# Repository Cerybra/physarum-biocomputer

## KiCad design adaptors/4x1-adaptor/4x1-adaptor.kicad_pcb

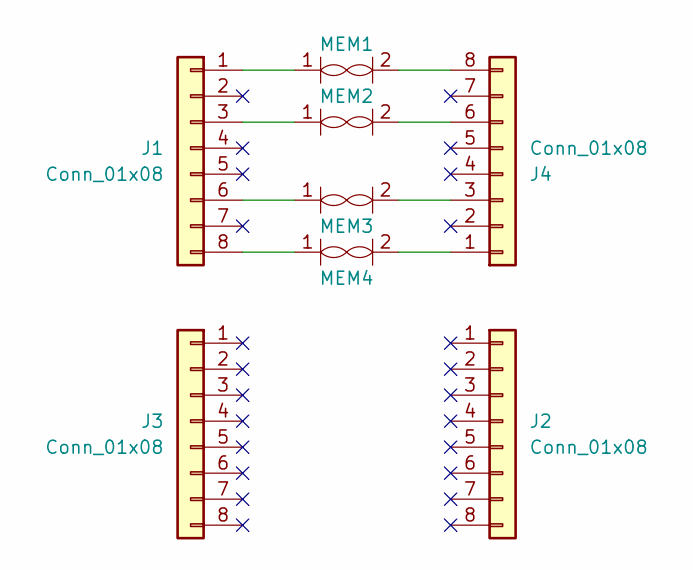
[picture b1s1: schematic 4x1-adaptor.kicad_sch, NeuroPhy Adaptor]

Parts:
J1, J2, J3, J4: Conn_01x08; PinHeader_1x08_P2.54mm_Vertical
MEM1, MEM2, MEM3, MEM4: NeuroPhy_Memristor_5x5mm

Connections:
unnamed: J1.1, MEM1.1
unnamed: J1.3, MEM2.1
unnamed: J1.6, MEM3.1
unnamed: J1.8, MEM4.1
unnamed: J4.1, MEM4.2
unnamed: J4.3, MEM3.2
unnamed: J4.6, MEM2.2
unnamed: J4.8, MEM1.2

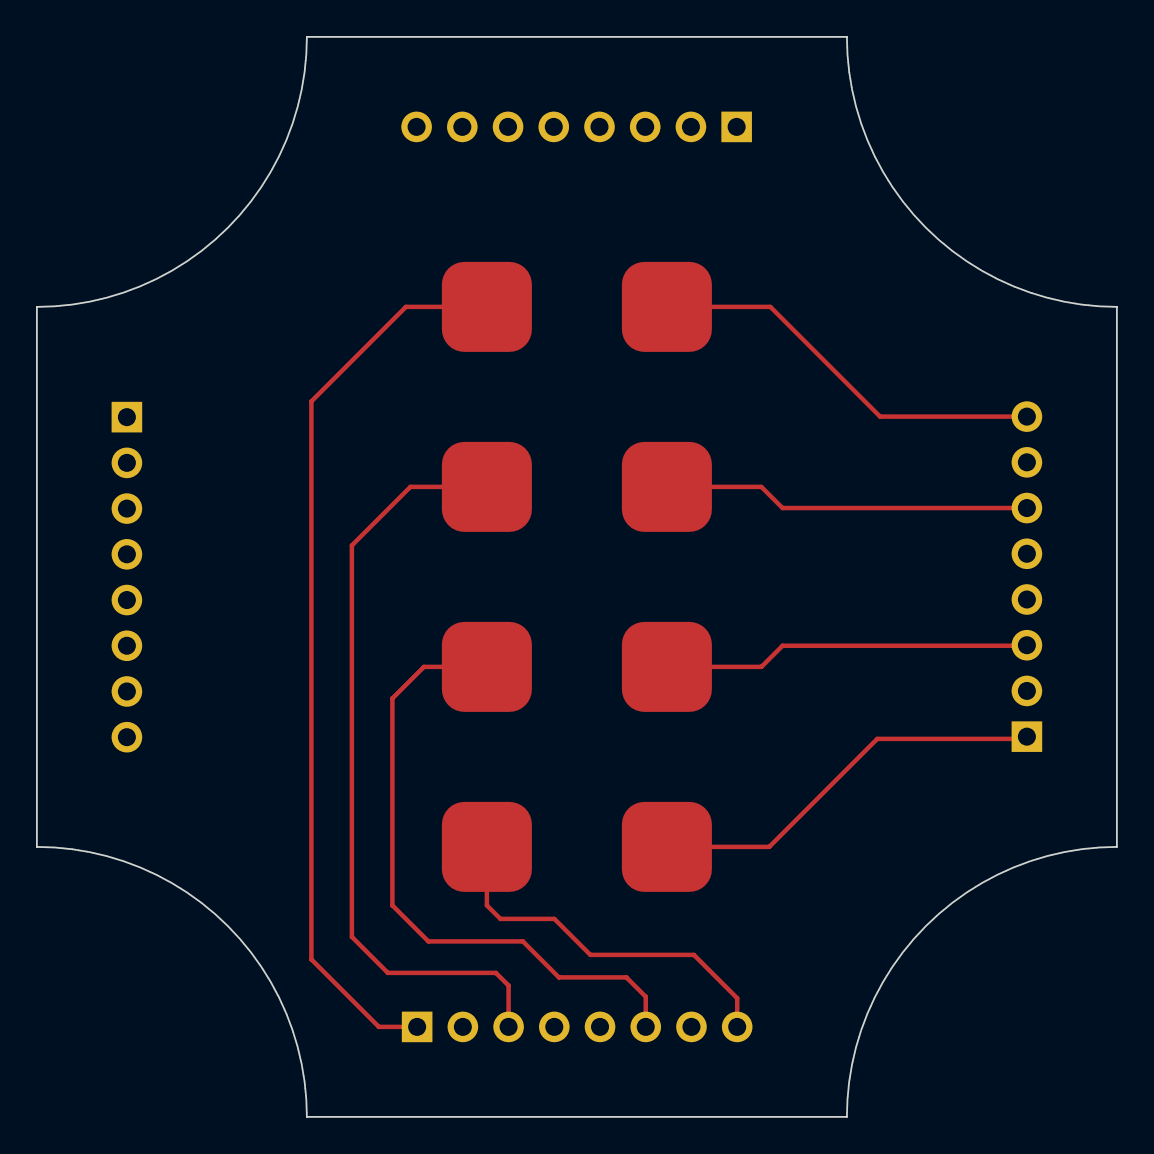
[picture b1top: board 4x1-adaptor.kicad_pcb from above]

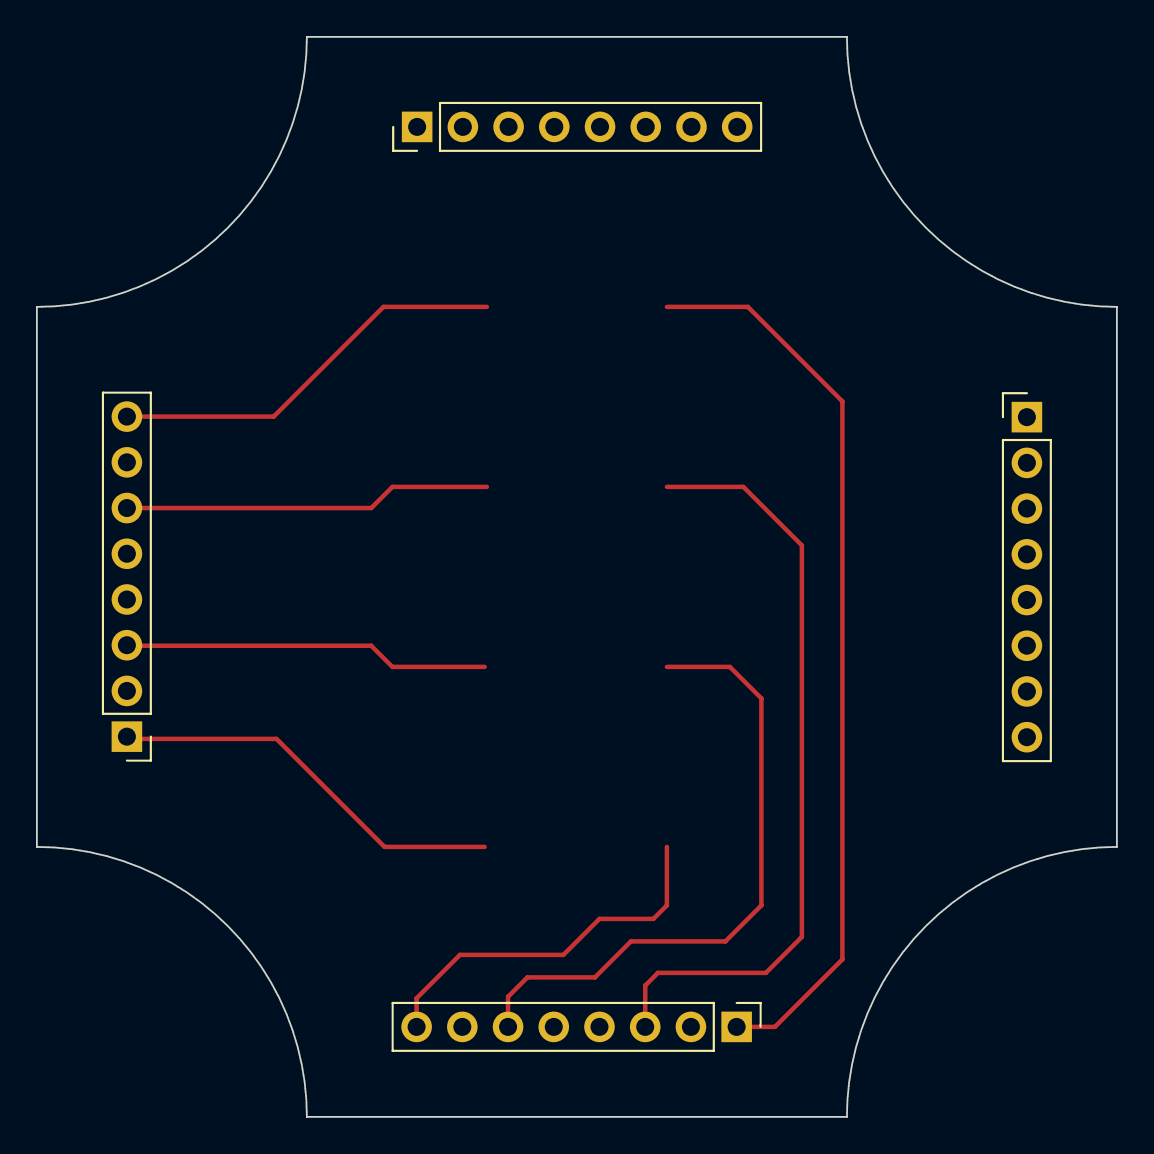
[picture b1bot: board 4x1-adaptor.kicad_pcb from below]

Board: 2 copper layers, 60.0 x 60.0 mm, 8 parts (4 on the bottom side), 8 nets.

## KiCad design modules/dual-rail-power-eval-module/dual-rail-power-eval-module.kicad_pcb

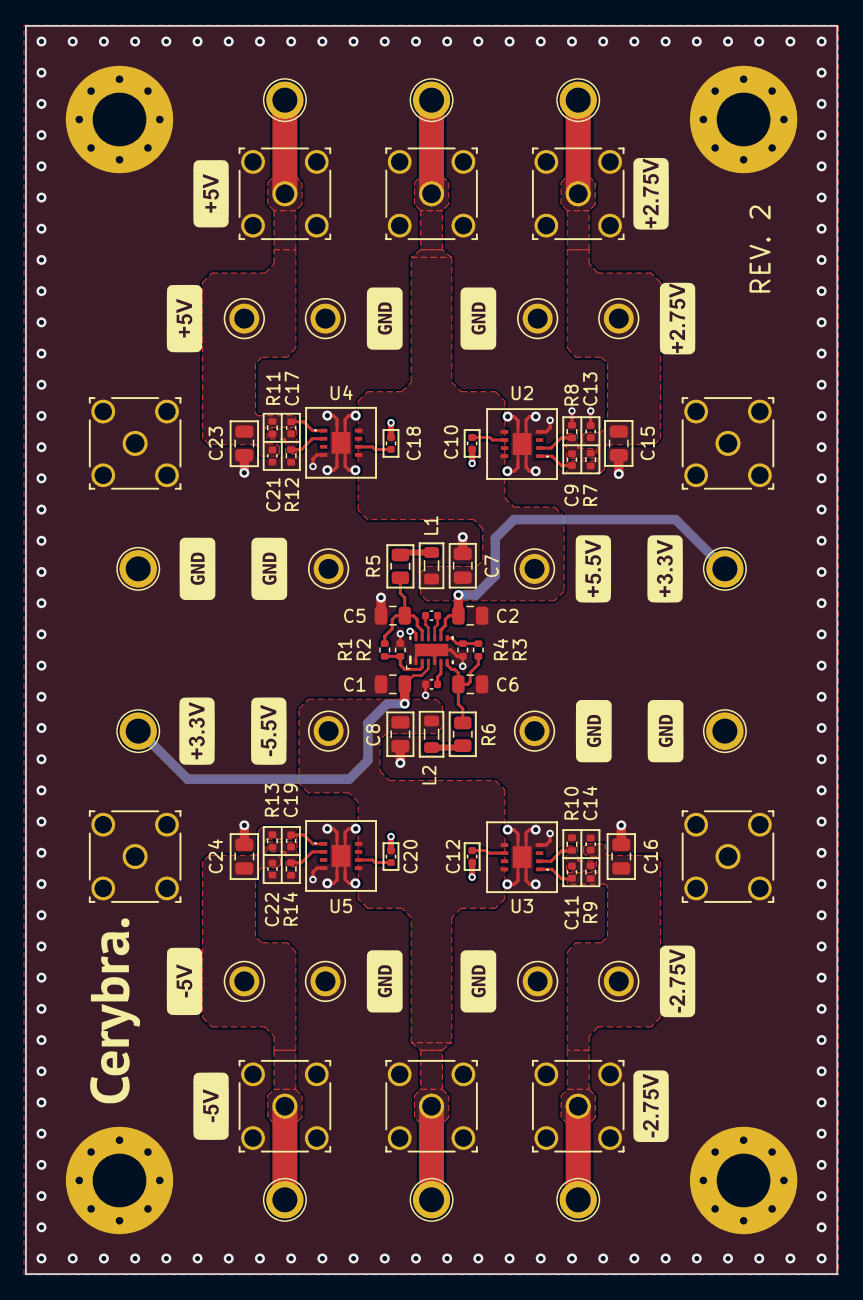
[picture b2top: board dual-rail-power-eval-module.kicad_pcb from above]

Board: 4 copper layers, 65.0 x 100.0 mm, 81 parts (0 on the bottom side), 25 nets.

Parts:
C1, C2, C15, C16, C23, C24: 10uF; C_0805_2012Metric
C3: 1uF; C_0402_1005Metric
C4: 4.7uF; C_0402_1005Metric
C5, C6: 22uF; C_0805_2012Metric
C7, C8: 100uF; C_0805_2012Metric
C9, C10, C11, C12, C17, C18, C19, C20: 10nF; C_0402_1005Metric
C13, C14, C21, C22: 100nF; C_0402_1005Metric
H1, H2, H3, H4: MountingHole_Pad; MountingHole_4.3mm_M4_Pad_Via
J1, J2, J3, J4, J5, J6, J7, J8, J9, J10: Conn_Coaxial; CONN_RF2-04A-T-00-50-G_ADM
L1, L2: 100uH; L_0805_2012Metric
R1, R3: 221k; R_0402_1005Metric
R2: 68.9k; R_0402_1005Metric
R4: 69.8k; R_0402_1005Metric
R5, R6: 1.3; R_0805_2012Metric
R7, R9: 47k; R_0402_1005Metric
R8, R10: 35k7; R_0402_1005Metric
R11, R13: 97k6; R_0402_1005Metric
R12, R14: 30k1; R_0402_1005Metric
TP1, TP2, TP3, TP4, TP5, TP6: TestPoint; KEYSTONE_5000
TP7, TP8, TP9, TP10, TP11, TP12: TestPoint; KEYSTONE_5006
TP13, TP14, TP15, TP16, TP17, TP18, TP19, TP20, TP21, TP22: Turret; TestPoint_Plated_Hole_D2.0mm
U1: LM27762; DSS0012B
U2, U4: TPS7A4901DRBR; VSON-8
U3, U5: TPS7A3001DRBR; VSON-8

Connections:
/+2.75V: C9.1, C13.1, C15.1, J3.1 (In), R7.2, TP3.1, TP16.1, U2.1 (OUT)
/+2.75V_REG_FB: C9.2, R7.1, R8.2, U2.2 (FB)
/+2.75V_REG_NR/SS: C10.1, U2.6 (NR/SS)
/+3.3V: C1.1, C2.1, TP13.1, TP17.1, U1.3 (VIN), U1.8 (EN-), U1.12 (EN+)
/+5.5V: C7.1, J1.1 (In), L1.2, TP1.1, TP14.1, U2.5 (EN), U2.8 (IN), U4.5 (EN), U4.8 (IN)
/+5V: C17.1, C21.1, C23.1, J5.1 (In), R11.2, TP5.1, TP15.1, U4.1 (OUT)
/+5V_REG_FB: C17.2, R11.1, R12.2, U4.2 (FB)
/+5V_REG_NR/SS: C18.1, U4.6 (NR/SS)
/-2.75V: C11.1, C14.1, C16.1, J4.1 (In), R9.2, TP4.1, TP20.1, U3.1 (OUT)
/-2.75V_REG_FB: C11.2, R9.1, R10.2, U3.2 (FB)
/-2.75V_REG_NR/SS: C12.1, U3.6 (NR/SS)
/-5.5V: C8.1, J2.1 (In), L2.2, TP2.1, TP18.1, U3.5 (EN), U3.8 (IN), U5.5 (EN), U5.8 (IN)
/-5V: C19.1, C22.1, C24.1, J6.1 (In), R13.2, TP6.1, TP19.1, U5.1 (OUT)
/-5V_REG_FB: C19.2, R13.1, R14.2, U5.2 (FB)
/-5V_REG_NR/SS: C20.1, U5.6 (NR/SS)
/C1+: C3.2, U1.10 (C1+)
/C1-: C3.1, U1.9 (C1-)
/CP_CAP: C4.1, U1.5 (CP)
/CP_NEG_FB: R3.1, R4.2, U1.7 (FB-)
/CP_NEG_OUT: C6.1, R3.2, R6.2, U1.6 (OUT-)
/CP_POS_FB: R1.1, R2.2, U1.2 (FB+)
/CP_POS_OUT: C5.1, R1.2, R5.2, U1.11 (OUT+)
Earth: C1.2, C2.2, C4.2, C5.2, C6.2, C7.2, C8.2, C10.2, C12.2, C13.2, C14.2, C15.2, C16.2, C18.2, C20.2, C21.2, C22.2, C23.2, C24.2, H1.1, H2.1, H3.1, H4.1, J1.2 (Ext), J2.2 (Ext), J3.2 (Ext), J4.2 (Ext), J5.2 (Ext), J6.2 (Ext), J7.1 (In), J7.2 (Ext), J8.1 (In), J8.2 (Ext), J9.1 (In), J9.2 (Ext), J10.1 (In), J10.2 (Ext), R2.1, R4.1, R8.1, R10.1, R12.1, R14.1, TP7.1, TP8.1, TP9.1, TP10.1, TP11.1, TP12.1, TP21.1, TP22.1, U1.1 (PGOOD), U1.4 (GND), U1.13 (GND), U2.4 (GND), U2.9 (EP), U2.10 (EP), U2.11 (EP), U2.12 (EP), U2.13 (EP), U3.4 (GND), U3.9 (EP), U3.10 (EP), U3.11 (EP), U3.12 (EP), U3.13 (EP), U4.4 (GND), U4.9 (EP), U4.10 (EP), U4.11 (EP), U4.12 (EP), U4.13 (EP), U5.4 (GND), U5.9 (EP), U5.10 (EP), U5.11 (EP), U5.12 (EP), U5.13 (EP)
unnamed: L1.1, R5.1
unnamed: L2.1, R6.1

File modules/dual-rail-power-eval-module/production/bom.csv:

Comment,Designator,Footprint,LCSC Part #
10uF Unpolarized capacitor,"C1,C2,C15,C16,C23,C24",C_0805_2012Metric,
1uF Unpolarized capacitor,C3,C_0402_1005Metric,
4.7uF Unpolarized capacitor,C4,C_0402_1005Metric,
22uF Unpolarized capacitor,"C5,C6",C_0805_2012Metric,
100uF Unpolarized capacitor,"C7,C8",C_0805_2012Metric,
10nF Unpolarized capacitor,"C9,C10,C11,C12,C17,C18,C19,C20",C_0402_1005Metric,
100nF Unpolarized capacitor,"C13,C14,C21,C22",C_0402_1005Metric,
"Conn_Coaxial coaxial connector (BNC, SMA, SMB, SMC, Cinch/RCA, LEMO, ...)","J1,J2,J3,J4,J5,J6,J7,J8,J9,J10",CONN_RF2-04A-T-00-50-G_ADM,C496549
100uH Inductor,"L1,L2",L_0805_2012Metric,
221k Resistor,"R1,R3",R_0402_1005Metric,
68k1 Resistor,R2,R_0402_1005Metric,
69k8 Resistor,R4,R_0402_1005Metric,
1.3 Resistor,"R5,R6",R_0805_2012Metric,
47k Resistor,"R7,R9",R_0402_1005Metric,
35k7 Resistor,"R8,R10",R_0402_1005Metric,
97k6 Resistor,"R11,R13",R_0402_1005Metric,
30k1 Resistor,"R12,R14",R_0402_1005Metric,
TestPoint test point,"TP1,TP2,TP3,TP4,TP5,TP6",KEYSTONE_5000,C5199900
TestPoint test point,"TP7,TP8,TP9,TP10,TP11,TP12",KEYSTONE_5006,C2906764
LM27762 ,U1,DSS0012B,
"TPS7A4901DRBR 36-V, 150-mA, Ultralow-Noise, Positive Linear Regulator","U2,U4",VSON-8,
"TPS7A3001DRBR –35-V, –200-mA, Ultralow-Noise, Negative Linear Regulator","U3,U5",VSON-8,
